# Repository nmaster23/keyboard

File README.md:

# Keyboard
This is a keyboard for YSWS which will be my first full keyboard (non macropad).

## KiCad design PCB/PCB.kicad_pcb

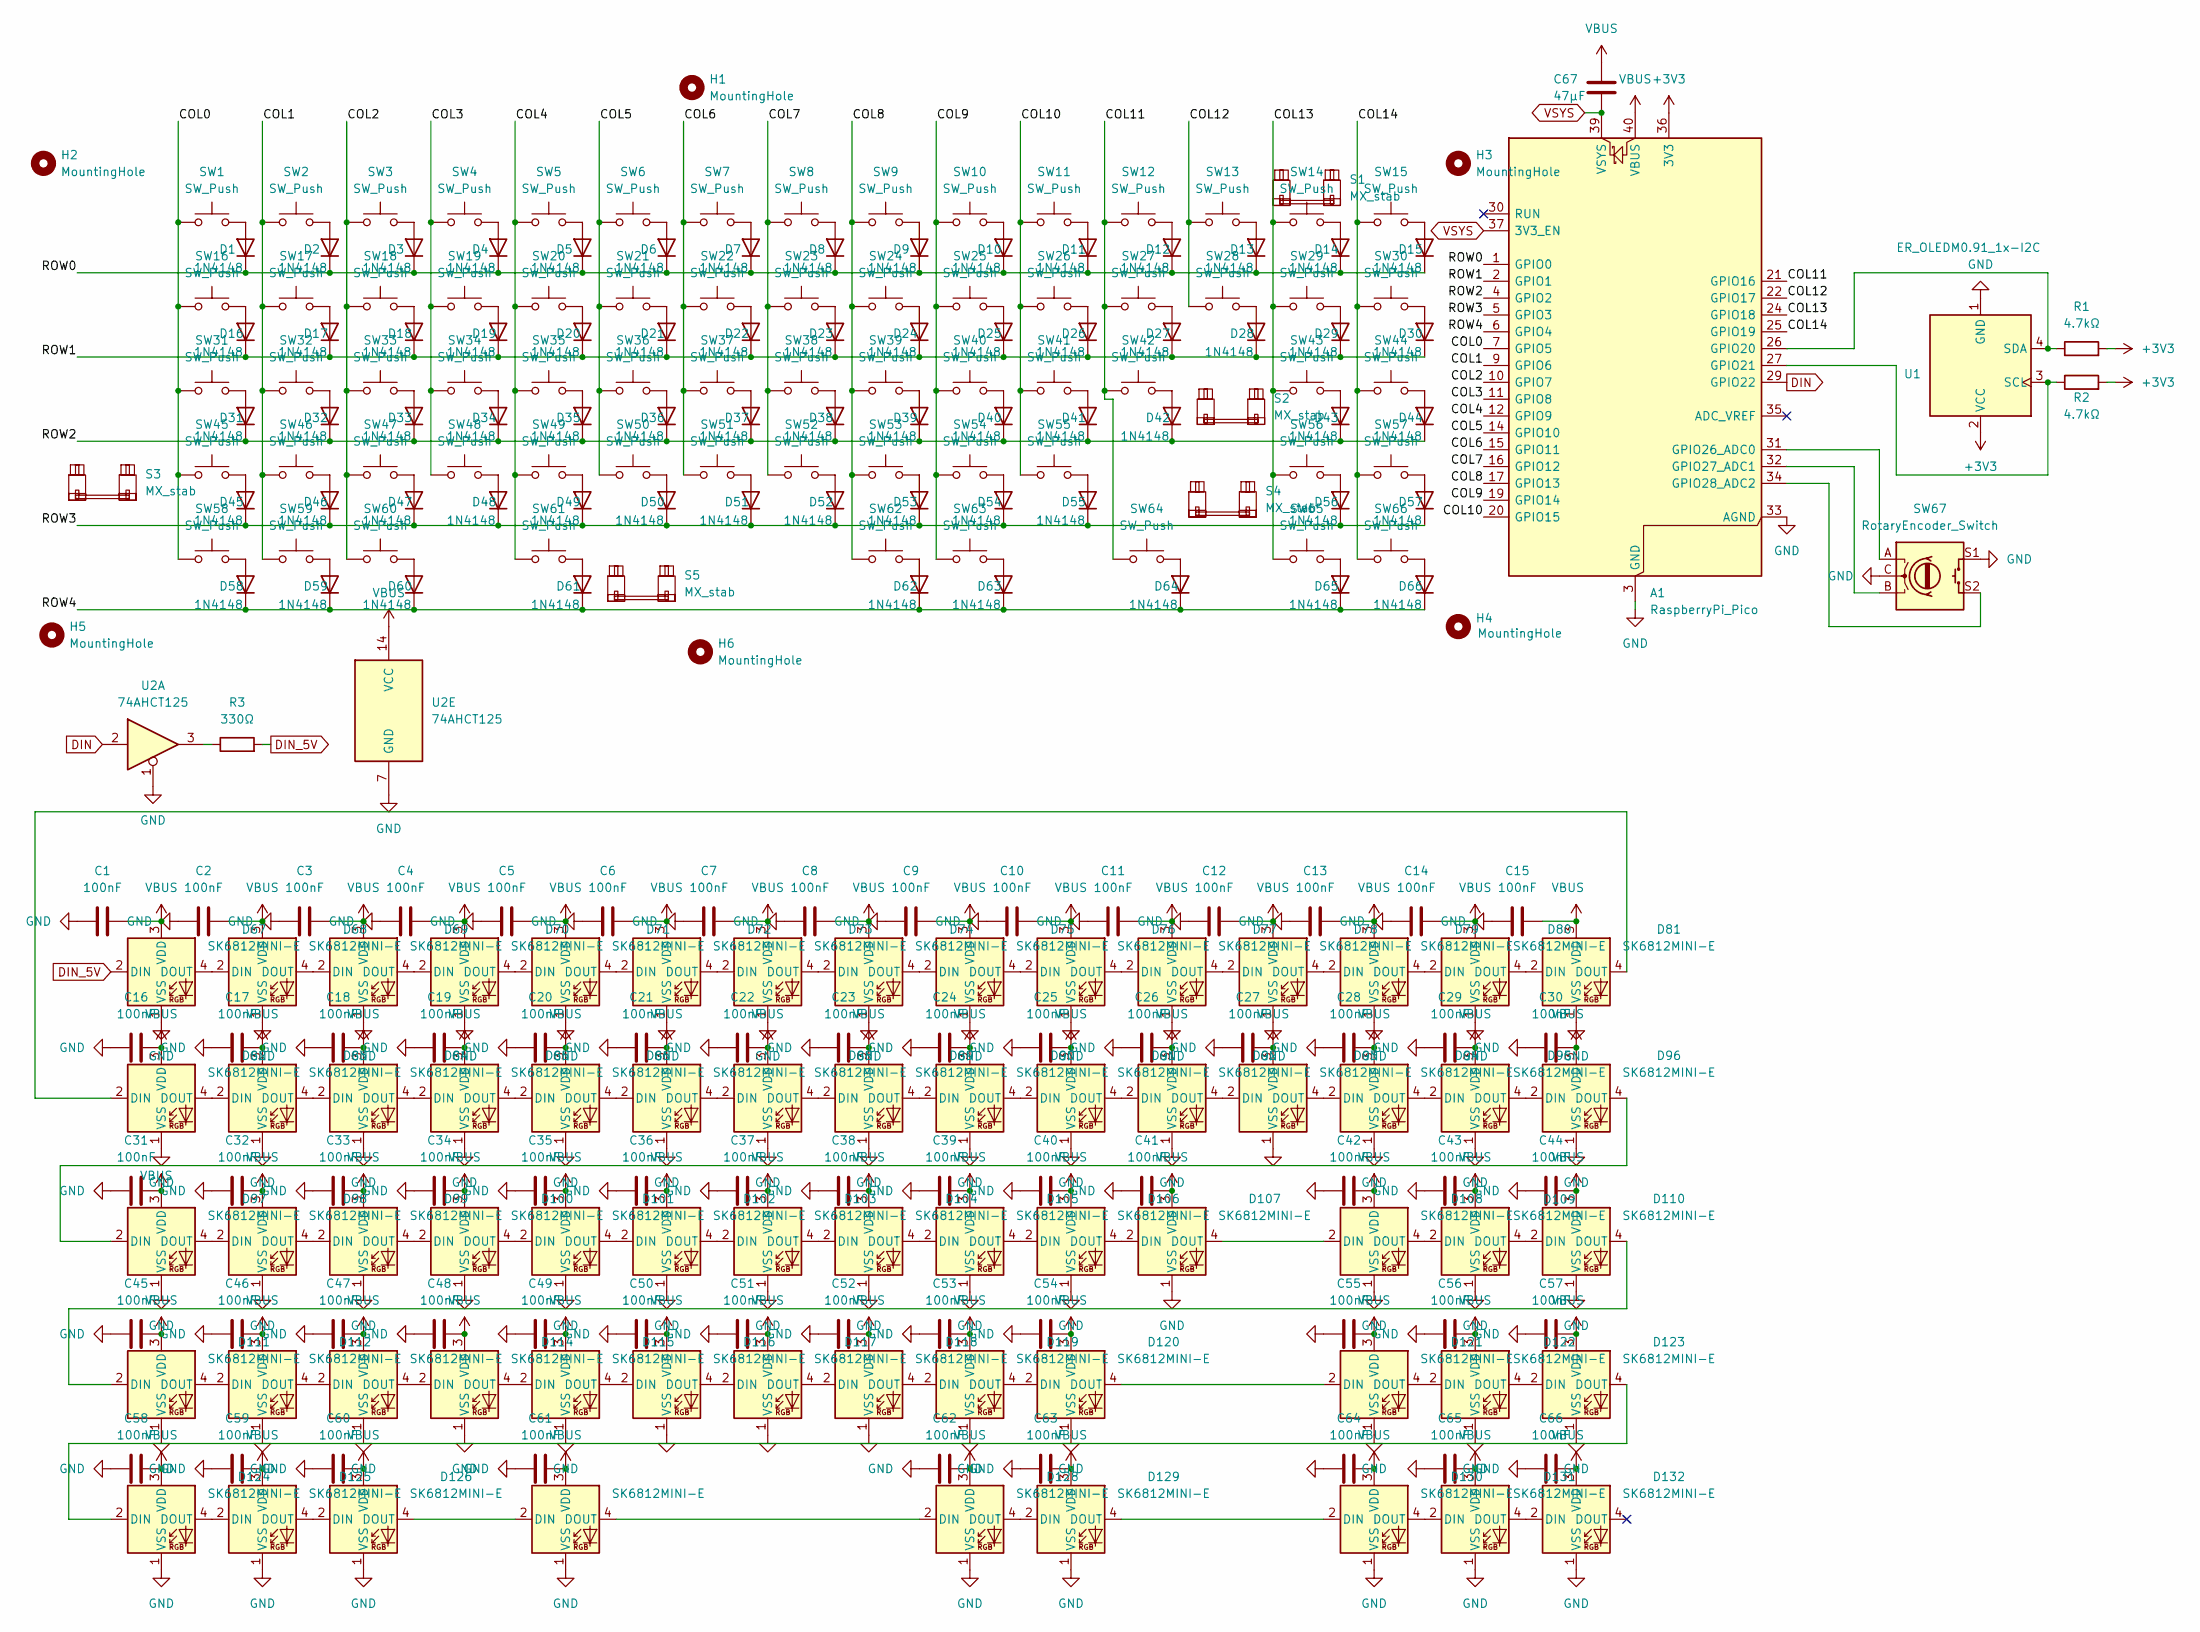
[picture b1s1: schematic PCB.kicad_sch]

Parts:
A1: RaspberryPi_Pico; RaspberryPi_Pico_Common_THT
C1, C2, C3, C4, C5, C6, C7, C8, C9, C10, C11, C12, C13, C14, C15, C16, C17, C18, C19, C20, C21, C22, C23, C24, C25, C26, C27, C28, C29, C30, C31, C32, C33, C34, C35, C36, C37, C38, C39, C40, C41, C42, C43, C44, C45, C46, C47, C48, C49, C50, C51, C52, C53, C54, C55, C56, C57, C58, C59, C60, C61, C62, C63, C64, C65, C66: 100nF; C_0805_2012Metric
C67: 47µF; C_1206_3216Metric
D1, D2, D3, D4, D5, D6, D7, D8, D9, D10, D11, D12, D13, D14, D15, D16, D17, D18, D19, D20, D21, D22, D23, D24, D25, D26, D27, D28, D29, D30, D31, D32, D33, D34, D35, D36, D37, D38, D39, D40, D41, D42, D43, D44, D45, D46, D47, D48, D49, D50, D51, D52, D53, D54, D55, D56, D57, D58, D59, D60, D61, D62, D63, D64, D65, D66: 1N4148; D_DO-35_SOD27_P7.62mm_Horizontal
D67, D68, D69, D70, D71, D72, D73, D74, D75, D76, D77, D78, D79, D80, D81, D82, D83, D84, D85, D86, D87, D88, D89, D90, D91, D92, D93, D94, D95, D96, D97, D98, D99, D100, D101, D102, D103, D104, D105, D106, D107, D108, D109, D110, D111, D112, D113, D114, D115, D116, D117, D118, D119, D120, D121, D122, D123, D124, D125, D126, D127, D128, D129, D130, D131, D132: SK6812MINI-E; LED_SK6812MINI-E_3.2x2.8mm_P1.5mm_ReverseMount
H1, H2, H3, H4, H5, H6: MountingHole; MountingHole_3.2mm_M3
R1, R2: 4.7kΩ; R_0805_2012Metric
R3: 330Ω; R_0805_2012Metric
S1: MX_stab; STAB_MX_2u
S2, S3: MX_stab; STAB_MX_2.25u
S4: MX_stab; STAB_MX_2.75u
S5: MX_stab; STAB_MX_P_6.25u
SW1, SW2, SW3, SW4, SW5, SW6, SW7, SW8, SW9, SW10, SW11, SW12, SW13, SW14, SW15, SW17, SW18, SW19, SW20, SW21, SW22, SW23, SW24, SW25, SW26, SW27, SW28, SW30, SW32, SW33, SW34, SW35, SW36, SW37, SW38, SW39, SW40, SW41, SW42, SW43, SW44, SW45, SW46, SW47, SW48, SW49, SW50, SW51, SW52, SW53, SW54, SW55, SW56, SW57, SW58, SW61, SW66: SW_Push; SW_MX_HS_CPG151101S11_1u
SW16, SW29: SW_Push; SW_MX_HS_CPG151101S11_1.5u
SW31: SW_Push; SW_MX_HS_CPG151101S11_1.75u
SW59, SW60, SW62, SW63, SW64, SW65: SW_Push; SW_MX_HS_CPG151101S11_1.25u
SW67: RotaryEncoder_Switch; RotaryEncoder_Alps_EC11E-Switch_Vertical_H20mm
U1: ER_OLEDM0.91_1x-I2C
U2: 74AHCT125; SOIC-14_3.9x8.7mm_P1.27mm

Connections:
+3V3: A1.36 (3V3), R1.2, R2.2, U1.2 (VCC); also elsewhere on the board
/COL0: A1.7 (GPIO5), SW1.1, SW16.1, SW31.1, SW45.1, SW58.1
/COL1: A1.9 (GPIO6), SW2.1, SW17.1, SW32.1, SW46.1, SW59.1
/COL2: A1.10 (GPIO7), SW3.1, SW18.1, SW33.1, SW47.1, SW60.1
/COL3: A1.11 (GPIO8), SW4.1, SW19.1, SW34.1, SW48.1
/COL4: A1.12 (GPIO9), SW5.1, SW20.1, SW35.1, SW49.1, SW61.1
/COL5: A1.14 (GPIO10), SW6.1, SW21.1, SW36.1, SW50.1
/COL6: A1.15 (GPIO11), SW7.1, SW22.1, SW37.1, SW51.1
/COL7: A1.16 (GPIO12), SW8.1, SW23.1, SW38.1, SW52.1
/COL8: A1.17 (GPIO13), SW9.1, SW24.1, SW39.1, SW53.1, SW62.1
/COL9: A1.19 (GPIO14), SW10.1, SW25.1, SW40.1, SW54.1, SW63.1
/COL10: A1.20 (GPIO15), SW11.1, SW26.1, SW41.1, SW55.1
/COL11: A1.21 (GPIO16), SW12.1, SW27.1, SW42.1, SW64.1
/COL12: A1.22 (GPIO17), SW13.1, SW28.1
/COL13: A1.24 (GPIO18), SW14.1, SW29.1, SW43.1, SW56.1, SW65.1
/COL14: A1.25 (GPIO19), SW15.1, SW30.1, SW44.1, SW57.1, SW66.1
/ROW0: A1.1 (GPIO0), D1.1 (K), D2.1 (K), D3.1 (K), D4.1 (K), D5.1 (K), D6.1 (K), D7.1 (K), D8.1 (K), D9.1 (K), D10.1 (K), D11.1 (K), D12.1 (K), D13.1 (K), D14.1 (K), D15.1 (K)
/ROW1: A1.2 (GPIO1), D16.1 (K), D17.1 (K), D18.1 (K), D19.1 (K), D20.1 (K), D21.1 (K), D22.1 (K), D23.1 (K), D24.1 (K), D25.1 (K), D26.1 (K), D27.1 (K), D28.1 (K), D29.1 (K), D30.1 (K)
/ROW2: A1.4 (GPIO2), D31.1 (K), D32.1 (K), D33.1 (K), D34.1 (K), D35.1 (K), D36.1 (K), D37.1 (K), D38.1 (K), D39.1 (K), D40.1 (K), D41.1 (K), D42.1 (K), D43.1 (K), D44.1 (K)
/ROW3: A1.5 (GPIO3), D45.1 (K), D46.1 (K), D47.1 (K), D48.1 (K), D49.1 (K), D50.1 (K), D51.1 (K), D52.1 (K), D53.1 (K), D54.1 (K), D55.1 (K), D56.1 (K), D57.1 (K)
/ROW4: A1.6 (GPIO4), D58.1 (K), D59.1 (K), D60.1 (K), D61.1 (K), D62.1 (K), D63.1 (K), D64.1 (K), D65.1 (K), D66.1 (K)
DIN: A1.29 (GPIO22), U2.2
DIN_5V: D67.2 (DIN), R3.2
GND: A1.3 (GND), A1.8 (GND), A1.13 (GND), A1.18 (GND), A1.23 (GND), A1.28 (GND), A1.33 (AGND), A1.38 (GND), C1.1, C2.1, C3.1, C4.1, C5.1, C6.1, C7.1, C8.1, C9.1, C10.1, C11.1, C12.1, C13.1, C14.1, C15.1, C16.1, C17.1, C18.1, C19.1, C20.1, C21.1, C22.1, C23.1, C24.1, C25.1, C26.1, C27.1, C28.1, C29.1, C30.1, C31.1, C32.1, C33.1, C34.1, C35.1, C36.1, C37.1, C38.1, C39.1, C40.1, C41.1, C42.1, C43.1, C44.1, C45.1, C46.1, C47.1, C48.1, C49.1, C50.1, C51.1, C52.1, C53.1, C54.1, C55.1, C56.1, C57.1, C58.1, C59.1, C60.1, C61.1, C62.1, C63.1, C64.1, C65.1, C66.1, D67.1 (VSS), D68.1 (VSS), D69.1 (VSS), D70.1 (VSS), D71.1 (VSS), D72.1 (VSS), D73.1 (VSS), D74.1 (VSS), D75.1 (VSS), D76.1 (VSS), D77.1 (VSS), D78.1 (VSS), D79.1 (VSS), D80.1 (VSS), D81.1 (VSS), D82.1 (VSS), D83.1 (VSS), D84.1 (VSS), D85.1 (VSS), D86.1 (VSS), D87.1 (VSS), D88.1 (VSS), D89.1 (VSS), D90.1 (VSS), D91.1 (VSS), D92.1 (VSS), D93.1 (VSS), D94.1 (VSS), D95.1 (VSS), D96.1 (VSS), D97.1 (VSS), D98.1 (VSS), D99.1 (VSS), D100.1 (VSS), D101.1 (VSS), D102.1 (VSS), D103.1 (VSS), D104.1 (VSS), D105.1 (VSS), D106.1 (VSS), D107.1 (VSS), D108.1 (VSS), D109.1 (VSS), D110.1 (VSS), D111.1 (VSS), D112.1 (VSS), D113.1 (VSS), D114.1 (VSS), D115.1 (VSS), D116.1 (VSS), D117.1 (VSS), D118.1 (VSS), D119.1 (VSS), D120.1 (VSS), D121.1 (VSS), D122.1 (VSS), D123.1 (VSS), D124.1 (VSS), D125.1 (VSS), D126.1 (VSS), D127.1 (VSS), D128.1 (VSS), D129.1 (VSS), D130.1 (VSS), D131.1 (VSS), D132.1 (VSS), SW67.C, SW67.S1, U1.1 (GND), U2.1, U2.7 (GND); also elsewhere on the board
unnamed: A1.26 (GPIO20), R1.1, U1.4 (SDA)
unnamed: A1.27 (GPIO21), R2.1, U1.3 (SCL)
unnamed: A1.31 (GPIO26_ADC0), SW67.A
unnamed: A1.32 (GPIO27_ADC1), SW67.B
unnamed: A1.34 (GPIO28_ADC2), SW67.S2
unnamed: D1.2 (A), SW1.2
unnamed: D2.2 (A), SW2.2
unnamed: D3.2 (A), SW3.2
unnamed: D4.2 (A), SW4.2
unnamed: D5.2 (A), SW5.2
unnamed: D6.2 (A), SW6.2
unnamed: D7.2 (A), SW7.2
unnamed: D8.2 (A), SW8.2
unnamed: D9.2 (A), SW9.2
unnamed: D10.2 (A), SW10.2
unnamed: D11.2 (A), SW11.2
unnamed: D12.2 (A), SW12.2
unnamed: D13.2 (A), SW13.2
unnamed: D14.2 (A), SW14.2
unnamed: D15.2 (A), SW15.2
unnamed: D16.2 (A), SW16.2
unnamed: D17.2 (A), SW17.2
unnamed: D18.2 (A), SW18.2
unnamed: D19.2 (A), SW19.2
unnamed: D20.2 (A), SW20.2
unnamed: D21.2 (A), SW21.2
unnamed: D22.2 (A), SW22.2
unnamed: D23.2 (A), SW23.2
unnamed: D24.2 (A), SW24.2
unnamed: D25.2 (A), SW25.2
unnamed: D26.2 (A), SW26.2
unnamed: D27.2 (A), SW27.2
unnamed: D28.2 (A), SW28.2
unnamed: D29.2 (A), SW29.2
unnamed: D30.2 (A), SW30.2
unnamed: D31.2 (A), SW31.2
unnamed: D32.2 (A), SW32.2
unnamed: D33.2 (A), SW33.2
unnamed: D34.2 (A), SW34.2
unnamed: D35.2 (A), SW35.2
unnamed: D36.2 (A), SW36.2
unnamed: D37.2 (A), SW37.2
unnamed: D38.2 (A), SW38.2
unnamed: D39.2 (A), SW39.2
unnamed: D40.2 (A), SW40.2
unnamed: D41.2 (A), SW41.2
unnamed: D42.2 (A), SW42.2
unnamed: D43.2 (A), SW43.2
unnamed: D44.2 (A), SW44.2
unnamed: D45.2 (A), SW45.2
unnamed: D46.2 (A), SW46.2
unnamed: D47.2 (A), SW47.2
unnamed: D48.2 (A), SW48.2
unnamed: D49.2 (A), SW49.2
unnamed: D50.2 (A), SW50.2
unnamed: D51.2 (A), SW51.2
unnamed: D52.2 (A), SW52.2
unnamed: D53.2 (A), SW53.2
unnamed: D54.2 (A), SW54.2
unnamed: D55.2 (A), SW55.2
unnamed: D56.2 (A), SW56.2
unnamed: D57.2 (A), SW57.2
unnamed: D58.2 (A), SW58.2
unnamed: D59.2 (A), SW59.2
unnamed: D60.2 (A), SW60.2
unnamed: D61.2 (A), SW61.2
unnamed: D62.2 (A), SW62.2
unnamed: D63.2 (A), SW63.2
unnamed: D64.2 (A), SW64.2
unnamed: D65.2 (A), SW65.2
unnamed: D66.2 (A), SW66.2
unnamed: D67.4 (DOUT), D68.2 (DIN)
unnamed: D68.4 (DOUT), D69.2 (DIN)
unnamed: D69.4 (DOUT), D70.2 (DIN)
unnamed: D70.4 (DOUT), D71.2 (DIN)
unnamed: D71.4 (DOUT), D72.2 (DIN)
unnamed: D72.4 (DOUT), D73.2 (DIN)
unnamed: D73.4 (DOUT), D74.2 (DIN)
unnamed: D74.4 (DOUT), D75.2 (DIN)
unnamed: D75.4 (DOUT), D76.2 (DIN)
unnamed: D76.4 (DOUT), D77.2 (DIN)
unnamed: D77.4 (DOUT), D78.2 (DIN)
unnamed: D78.4 (DOUT), D79.2 (DIN)
unnamed: D79.4 (DOUT), D80.2 (DIN)
unnamed: D80.4 (DOUT), D81.2 (DIN)
unnamed: D81.4 (DOUT), D82.2 (DIN)
unnamed: D82.4 (DOUT), D83.2 (DIN)
unnamed: D83.4 (DOUT), D84.2 (DIN)
unnamed: D84.4 (DOUT), D85.2 (DIN)
unnamed: D85.4 (DOUT), D86.2 (DIN)
unnamed: D86.4 (DOUT), D87.2 (DIN)
unnamed: D87.4 (DOUT), D88.2 (DIN)
unnamed: D88.4 (DOUT), D89.2 (DIN)
unnamed: D89.4 (DOUT), D90.2 (DIN)
unnamed: D90.4 (DOUT), D91.2 (DIN)
unnamed: D91.4 (DOUT), D92.2 (DIN)
unnamed: D92.4 (DOUT), D93.2 (DIN)
unnamed: D93.4 (DOUT), D94.2 (DIN)
unnamed: D94.4 (DOUT), D95.2 (DIN)
unnamed: D95.4 (DOUT), D96.2 (DIN)
unnamed: D96.4 (DOUT), D97.2 (DIN)
unnamed: D97.4 (DOUT), D98.2 (DIN)
unnamed: D98.4 (DOUT), D99.2 (DIN)
unnamed: D99.4 (DOUT), D100.2 (DIN)
unnamed: D100.4 (DOUT), D101.2 (DIN)
unnamed: D101.4 (DOUT), D102.2 (DIN)
unnamed: D102.4 (DOUT), D103.2 (DIN)
unnamed: D103.4 (DOUT), D104.2 (DIN)
unnamed: D104.4 (DOUT), D105.2 (DIN)
unnamed: D105.4 (DOUT), D106.2 (DIN)
unnamed: D106.4 (DOUT), D107.2 (DIN)
unnamed: D107.4 (DOUT), D108.2 (DIN)
unnamed: D108.4 (DOUT), D109.2 (DIN)
unnamed: D109.4 (DOUT), D110.2 (DIN)
unnamed: D110.4 (DOUT), D111.2 (DIN)
unnamed: D111.4 (DOUT), D112.2 (DIN)
unnamed: D112.4 (DOUT), D113.2 (DIN)
unnamed: D113.4 (DOUT), D114.2 (DIN)
unnamed: D114.4 (DOUT), D115.2 (DIN)
unnamed: D115.4 (DOUT), D116.2 (DIN)
unnamed: D116.4 (DOUT), D117.2 (DIN)
unnamed: D117.4 (DOUT), D118.2 (DIN)
unnamed: D118.4 (DOUT), D119.2 (DIN)
unnamed: D119.4 (DOUT), D120.2 (DIN)
unnamed: D120.4 (DOUT), D121.2 (DIN)
unnamed: D121.4 (DOUT), D122.2 (DIN)
unnamed: D122.4 (DOUT), D123.2 (DIN)
unnamed: D123.4 (DOUT), D124.2 (DIN)
unnamed: D124.4 (DOUT), D125.2 (DIN)
unnamed: D125.4 (DOUT), D126.2 (DIN)
unnamed: D126.4 (DOUT), D127.2 (DIN)
unnamed: D127.4 (DOUT), D128.2 (DIN)
unnamed: D128.4 (DOUT), D129.2 (DIN)
unnamed: D129.4 (DOUT), D130.2 (DIN)
unnamed: D130.4 (DOUT), D131.2 (DIN)
unnamed: D131.4 (DOUT), D132.2 (DIN)
unnamed: R3.1, U2.3
VBUS: A1.40 (VBUS), C1.2, C2.2, C3.2, C4.2, C5.2, C6.2, C7.2, C8.2, C9.2, C10.2, C11.2, C12.2, C13.2, C14.2, C15.2, C16.2, C17.2, C18.2, C19.2, C20.2, C21.2, C22.2, C23.2, C24.2, C25.2, C26.2, C27.2, C28.2, C29.2, C30.2, C31.2, C32.2, C33.2, C34.2, C35.2, C36.2, C37.2, C38.2, C39.2, C40.2, C41.2, C42.2, C43.2, C44.2, C45.2, C46.2, C47.2, C48.2, C49.2, C50.2, C51.2, C52.2, C53.2, C54.2, C55.2, C56.2, C57.2, C58.2, C59.2, C60.2, C61.2, C62.2, C63.2, C64.2, C65.2, C66.2, C67.1, D67.3 (VDD), D68.3 (VDD), D69.3 (VDD), D70.3 (VDD), D71.3 (VDD), D72.3 (VDD), D73.3 (VDD), D74.3 (VDD), D75.3 (VDD), D76.3 (VDD), D77.3 (VDD), D78.3 (VDD), D79.3 (VDD), D80.3 (VDD), D81.3 (VDD), D82.3 (VDD), D83.3 (VDD), D84.3 (VDD), D85.3 (VDD), D86.3 (VDD), D87.3 (VDD), D88.3 (VDD), D89.3 (VDD), D90.3 (VDD), D91.3 (VDD), D92.3 (VDD), D93.3 (VDD), D94.3 (VDD), D95.3 (VDD), D96.3 (VDD), D97.3 (VDD), D98.3 (VDD), D99.3 (VDD), D100.3 (VDD), D101.3 (VDD), D102.3 (VDD), D103.3 (VDD), D104.3 (VDD), D105.3 (VDD), D106.3 (VDD), D107.3 (VDD), D108.3 (VDD), D109.3 (VDD), D110.3 (VDD), D111.3 (VDD), D112.3 (VDD), D113.3 (VDD), D114.3 (VDD), D115.3 (VDD), D116.3 (VDD), D117.3 (VDD), D118.3 (VDD), D119.3 (VDD), D120.3 (VDD), D121.3 (VDD), D122.3 (VDD), D123.3 (VDD), D124.3 (VDD), D125.3 (VDD), D126.3 (VDD), D127.3 (VDD), D128.3 (VDD), D129.3 (VDD), D130.3 (VDD), D131.3 (VDD), D132.3 (VDD), U2.14 (VCC)
VSYS: A1.37 (3V3_EN), A1.39 (VSYS), C67.2

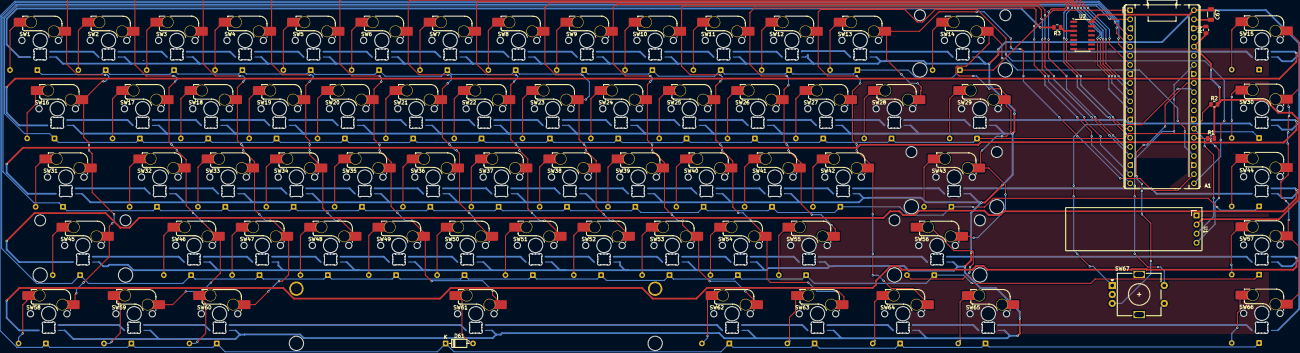
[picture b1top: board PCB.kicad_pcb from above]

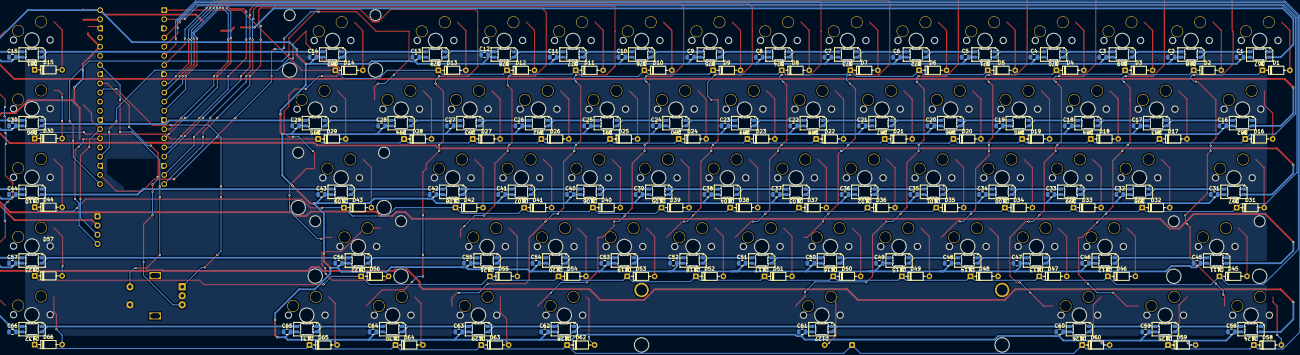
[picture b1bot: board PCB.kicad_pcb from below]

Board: 2 copper layers, 284 parts (197 on the bottom side), 163 nets.

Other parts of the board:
R4: 10kΩ; R_0805_2012Metric

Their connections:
+3V3: R4.1; also elsewhere on the board
GND: R4.2; also elsewhere on the board
